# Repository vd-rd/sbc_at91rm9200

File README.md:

## Overview
This module, based on Microchip (Atmel) AT91RM9200 microprocessor, is intended as a learning exercise in designing an embedded Linux development board suitable for IoT and other applications.
 All the board resources and documentation are open source and can be contributed to.
 Detailed documentation, as well as resources used can be found in the [docs](docs) and [resources](resources) folders.

### Key features
 * Low price for an embedded Linux system;
 * Medium difficulty to assemble at home;
 * Documented features and mainline support in kernel.

### Specifications
  * AT91RM9200 microprocessor @ 190MHz;
  * 64MB SDRAM @ 90MHz;
  * 2MB DataFlash memory for U-boot and environment storage;
  * MicroSD connector for RootFS and user storage;
  * Expansion headers with common functions available (USART, SPI, I2C, RMII, USB Host, etc.);
  * USB client connector.

### Todo
 * build the board
 * gather the components
 * test the board
 * build optimised U-Boot and Busybox

### Resources
You can find all necesary information to build or evaluate the module here:
   - [View layout and schematic](https://cadlab.io/project/1679) ;
   - [View 3D board render](https://a360.co/2G43pcl);
   - [Fabrication files](https://github.com/vd-rd/sbc_at91rm9200/releases);

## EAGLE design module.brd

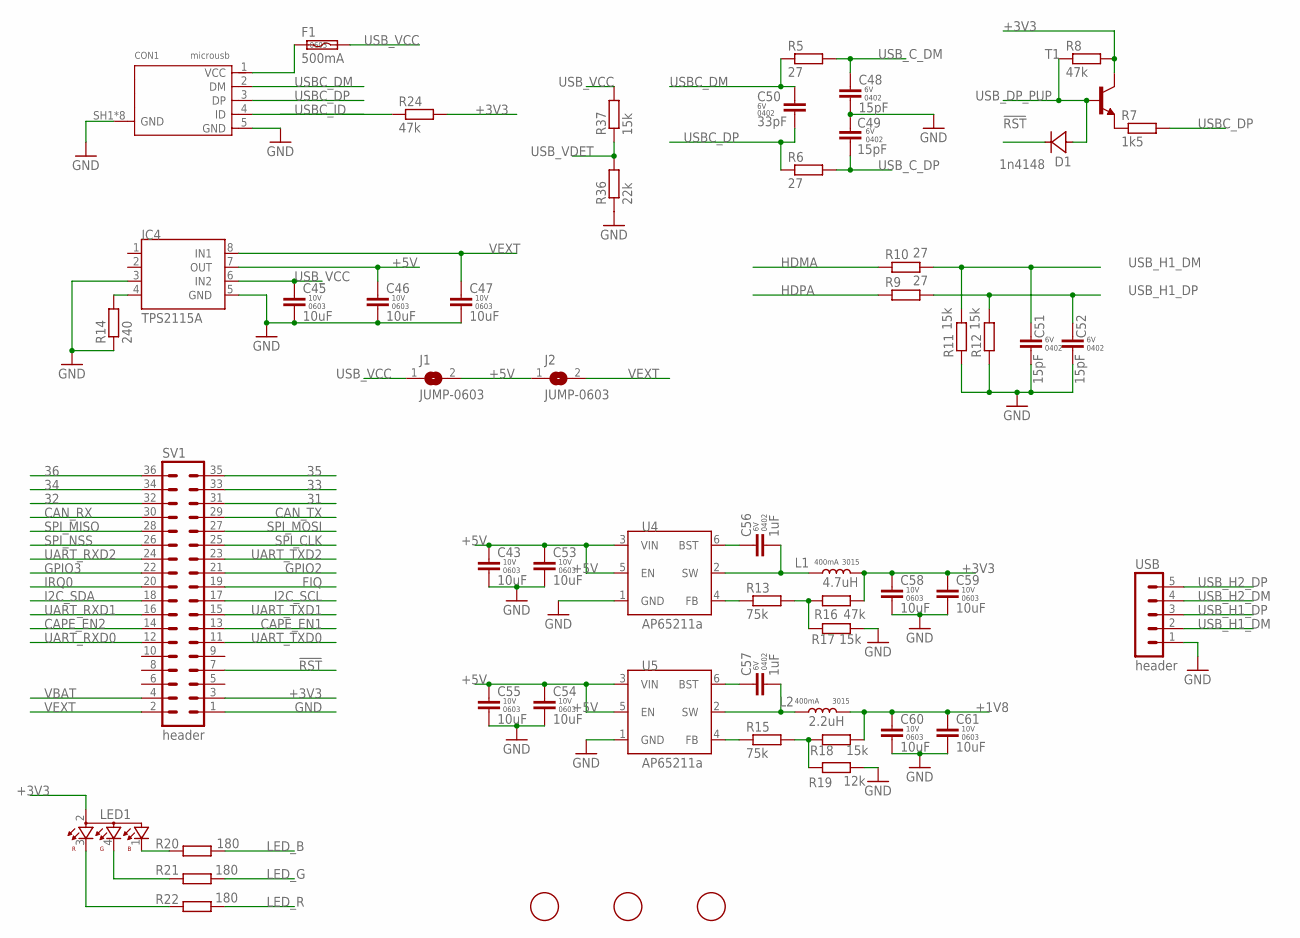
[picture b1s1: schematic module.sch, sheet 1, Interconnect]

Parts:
C43, C45, C46, C47, C53, C54, C55, C58, C59, C60, C61: 10uF; C0603
C48, C49, C51, C52: 15pF; C0402K
C50: 33pF; C0402K
C56, C57: 1uF; C0402K
CON1: microusb; 10118194
D1: 1n4148; SOD323
F1: 500mA; F0603
IC4: TPS2115A; TSSOP8
J1, J2: JUMP-0603; C0603
L1: 4.7uH; L3230M
L2: 2.2uH; L3230M
LED1: OSTB1204C1E; 321015RGB
R5, R6, R9, R10: 27; R0402
R7: 1k5; R0402
R8, R16, R24: 47k; R0402
R11, R12, R17, R18, R37: 15k; R0402
R13, R15: 75k; R0402
R14: 240; R0402
R19: 12k; R0402
R20, R21, R22: 180; R0402
R36: 22k; R0402
SV1: header; MA18-2
T1: MMBT2222ALT1-NPN-SOT23-BEC; SOT23-BEC
U4, U5: AP65211A; SOT95P280X110-6
U$1, U$2, U$3: FIDUCIAL; FIDUCIAL_1MM
USB: header; MA05-1

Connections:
31: SV1.31; also elsewhere on the board
32: SV1.32; also elsewhere on the board
33: SV1.33; also elsewhere on the board
34: SV1.34; also elsewhere on the board
35: SV1.35; also elsewhere on the board
36: SV1.36; also elsewhere on the board
!RST: D1.K (C), SV1.7; also elsewhere on the board
+1V8: C60.1, C61.1, L2.2, R18.2; also elsewhere on the board
+3V3: C58.1, C59.1, L1.2, LED1.2, R8.2, R16.2, R24.2, SV1.3, T1.C; also elsewhere on the board
+5V: C43.1, C46.1, C53.1, C54.1, C55.1, IC4.7 (OUT), J1.2, J2.1, U4.3 (VIN), U4.5 (EN), U5.3 (VIN), U5.5 (EN)
CAN_RX: SV1.30
CAN_TX: SV1.29
CAPE_EN1: SV1.13; also elsewhere on the board
CAPE_EN2: SV1.14; also elsewhere on the board
FIQ: SV1.19; also elsewhere on the board
GND: C43.2, C45.2, C46.2, C47.2, C48.2, C49.2, C51.2, C52.2, C53.2, C54.2, C55.2, C58.2, C59.2, C60.2, C61.2, CON1.5 (GND), CON1.SH1 (GND), CON1.SH2 (GND), CON1.SH3 (GND), CON1.SH4 (GND), CON1.SH5 (GND), CON1.SH6 (GND), CON1.SH7 (GND), CON1.SH8 (GND), IC4.3, IC4.5 (GND), R11.1, R12.1, R14.1, R17.2, R19.2, R36.1, SV1.1, U4.1 (GND), U5.1 (GND), USB.1; also elsewhere on the board
GPIO2: SV1.21; also elsewhere on the board
GPIO3: SV1.22; also elsewhere on the board
HDMA: R10.1; also elsewhere on the board
HDPA: R9.1; also elsewhere on the board
I2C_SCL: SV1.17; also elsewhere on the board
I2C_SDA: SV1.18; also elsewhere on the board
IRQ0: SV1.20; also elsewhere on the board
LED_B: R20.1; also elsewhere on the board
LED_G: R21.1; also elsewhere on the board
LED_R: R22.1; also elsewhere on the board
unnamed: C56.2, L1.1, U4.2 (SW)
unnamed: CON1.1 (VCC), F1.1
unnamed: IC4.4, R14.2
unnamed: C57.2, L2.1, U5.2 (SW)
unnamed: LED1.1, R20.2
unnamed: C56.1, U4.6 (BST)
unnamed: C57.1, U5.6 (BST)
unnamed: LED1.4, R21.2
unnamed: R15.1, U5.4 (FB)
unnamed: R7.1, T1.E
unnamed: R13.1, U4.4 (FB)
unnamed: R15.2, R18.1, R19.1
unnamed: R13.2, R16.1, R17.1
unnamed: LED1.3, R22.2
SPI_CLK: SV1.25; also elsewhere on the board
SPI_MISO: SV1.28; also elsewhere on the board
SPI_MOSI: SV1.27; also elsewhere on the board
SPI_NSS: SV1.26; also elsewhere on the board
UART_RXD0: SV1.12; also elsewhere on the board
UART_RXD1: SV1.16; also elsewhere on the board
UART_RXD2: SV1.24; also elsewhere on the board
UART_TXD0: SV1.11; also elsewhere on the board
UART_TXD1: SV1.15; also elsewhere on the board
UART_TXD2: SV1.23; also elsewhere on the board
USBC_DM: C50.1, CON1.2 (DM), R5.1
USBC_DP: C50.2, CON1.3 (DP), R6.1, R7.2
USBC_ID: CON1.4 (ID), R24.1; also elsewhere on the board
USB_C_DM: C48.1, R5.2; also elsewhere on the board
USB_C_DP: C49.1, R6.2; also elsewhere on the board
USB_DP_PUP: D1.A, R8.1, T1.B; also elsewhere on the board
USB_H1_DM: C51.1, R10.2, R11.2, USB.2
USB_H1_DP: C52.1, R9.2, R12.2, USB.3
USB_H2_DM: USB.4
USB_H2_DP: USB.5
USB_VCC: C45.1, F1.2, IC4.6 (IN2), J1.1, R37.2
USB_VDET: R36.2, R37.1; also elsewhere on the board
VBAT: SV1.4
VEXT: C47.1, IC4.8 (IN1), J2.2, SV1.2

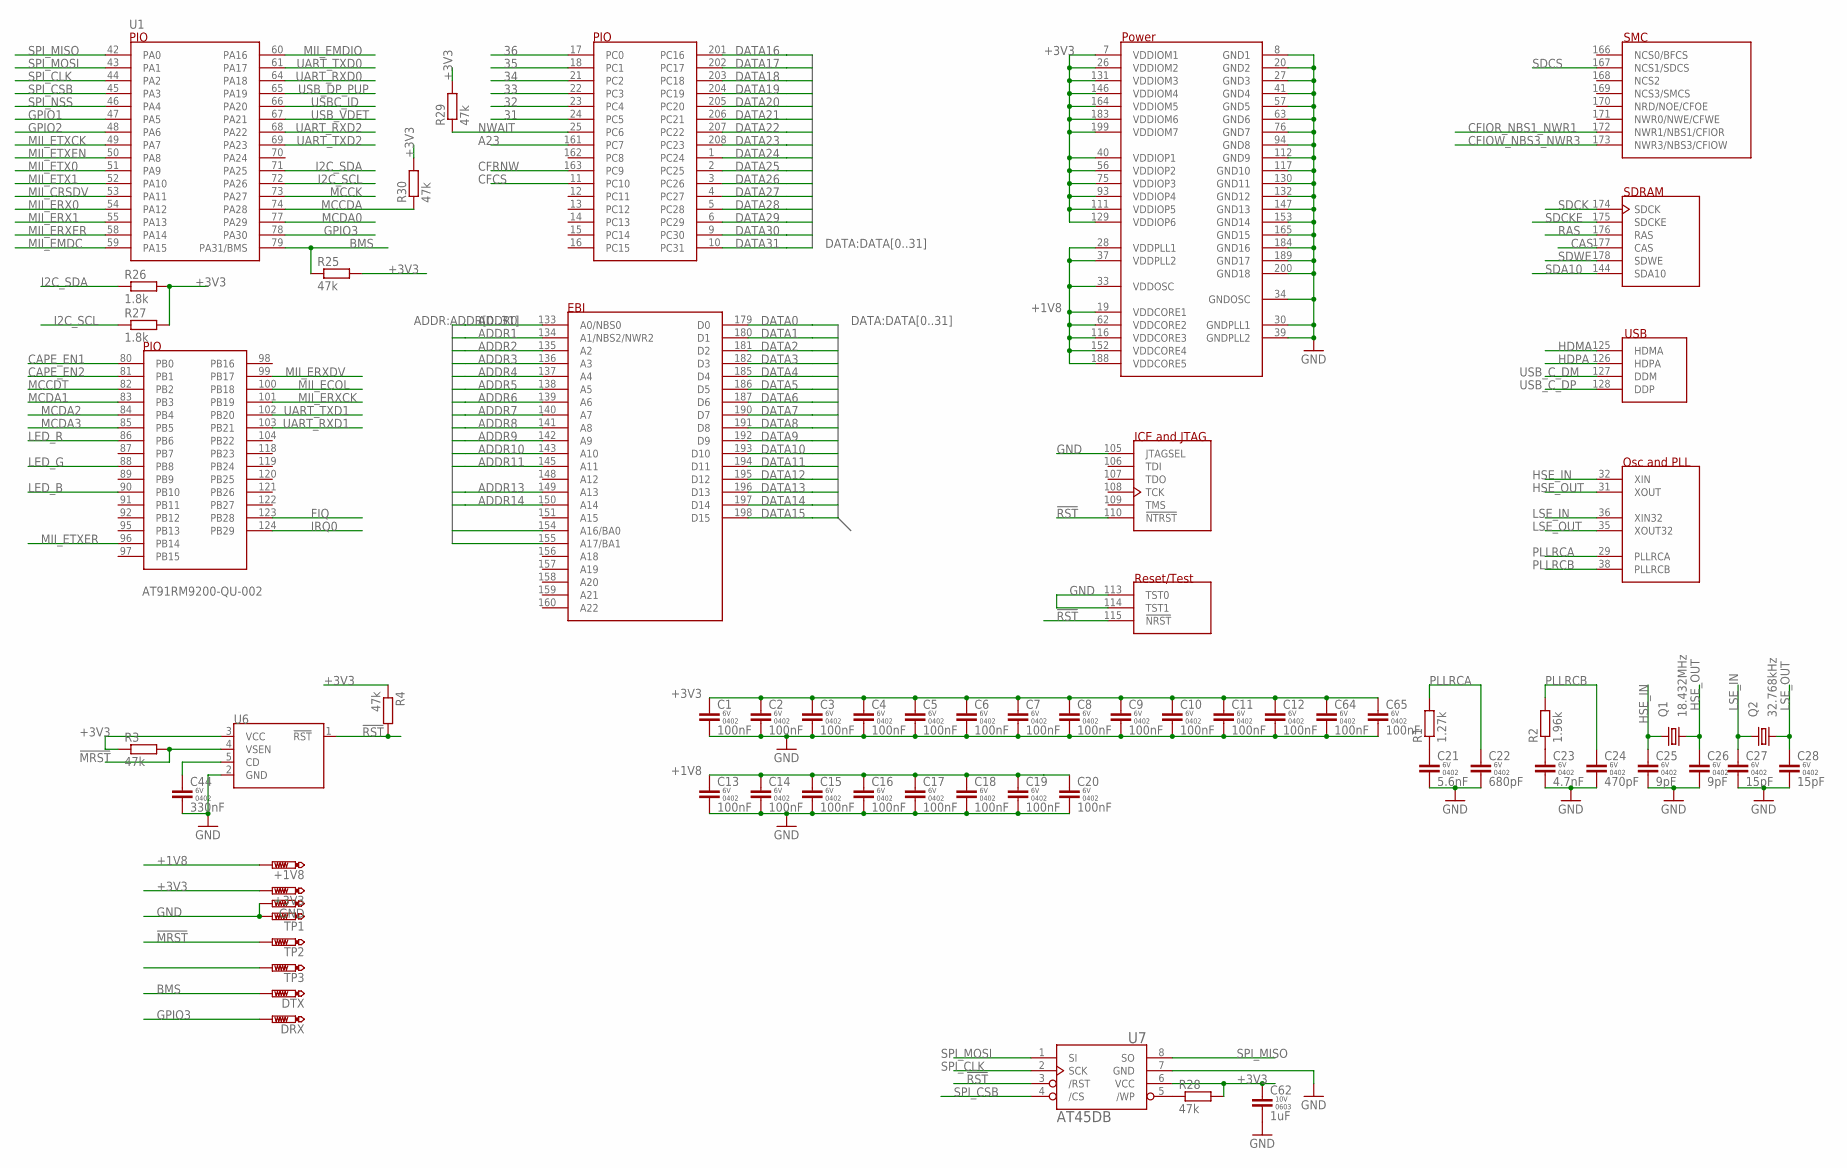
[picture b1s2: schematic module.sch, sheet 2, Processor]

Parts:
+1V8, +3V3: PTR1B1,27; B1,27
C1, C2, C3, C4, C5, C6, C7, C8, C9, C10, C11, C12, C13, C14, C15, C16, C17, C18, C19, C20, C64, C65: 100nF; C0402K
C21: 5.6nF; C0402K
C22: 680pF; C0402K
C23: 4.7nF; C0402K
C24: 470pF; C0402K
C25, C26: 9pF; C0402K
C27, C28: 15pF; C0402K
C44: 330nF; C0402K
C62: 1uF; C0603
DRX: PTR1B1,27; B1,27
DTX: PTR1B1,27; B1,27
GND: PTR1B1,27; B1,27
Q1: 18.432MHz; 3215
Q2: 32.768kHz; 3215
R1: 1.27k; R0402
R2: 1.96k; R0402
R3, R4, R25, R28, R29, R30: 47k; R0402
R26, R27: 1.8k; R0402
TP1, TP2, TP3: PTR1B1,27; B1,27
U1: AT91RM9200-QU-002; QFP50P3120X3120X410-208N
U6: STM1831; SOT95P280X100-5
U7: AT45DB-S; SO08-208

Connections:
31: U1.24 (PC5); also elsewhere on the board
32: U1.23 (PC4); also elsewhere on the board
33: U1.22 (PC3); also elsewhere on the board
34: U1.21 (PC2); also elsewhere on the board
35: U1.18 (PC1); also elsewhere on the board
36: U1.17 (PC0); also elsewhere on the board
!MRST: R3.2, TP2.TP, U6.4 (VSEN)
!RST: R4.2, U1.110 (!NTRST), U1.115 (!NRST), U6.1 (!RST), U7.3 (/RST); also elsewhere on the board
+1V8: +1V8.TP, C13.1, C14.1, C15.1, C16.1, C17.1, C18.1, C19.1, C20.1, U1.19 (VDDCORE1), U1.28 (VDDPLL1), U1.33 (VDDOSC), U1.37 (VDDPLL2), U1.62 (VDDCORE2), U1.116 (VDDCORE3), U1.152 (VDDCORE4), U1.188 (VDDCORE5); also elsewhere on the board
+3V3: +3V3.TP, C1.1, C2.1, C3.1, C4.1, C5.1, C6.1, C7.1, C8.1, C9.1, C10.1, C11.1, C12.1, C62.1, C64.1, C65.1, R3.1, R4.1, R25.2, R26.2, R27.2, R28.2, R29.2, R30.2, U1.7 (VDDIOM1), U1.26 (VDDIOM2), U1.40 (VDDIOP1), U1.56 (VDDIOP2), U1.75 (VDDIOP3), U1.93 (VDDIOP4), U1.111 (VDDIOP5), U1.129 (VDDIOP6), U1.131 (VDDIOM3), U1.146 (VDDIOM4), U1.164 (VDDIOM5), U1.183 (VDDIOM6), U1.199 (VDDIOM7), U6.3 (VCC), U7.6 (VCC); also elsewhere on the board
A23: U1.161 (PC7)
ADDR0: U1.133 (A0/NBS0); also elsewhere on the board
ADDR1: U1.134 (A1/NBS2/NWR2); also elsewhere on the board
ADDR2: U1.135 (A2); also elsewhere on the board
ADDR3: U1.136 (A3); also elsewhere on the board
ADDR4: U1.137 (A4); also elsewhere on the board
ADDR5: U1.138 (A5); also elsewhere on the board
ADDR6: U1.139 (A6); also elsewhere on the board
ADDR7: U1.140 (A7); also elsewhere on the board
ADDR8: U1.141 (A8); also elsewhere on the board
ADDR9: U1.142 (A9); also elsewhere on the board
ADDR10: U1.143 (A10); also elsewhere on the board
ADDR11: U1.145 (A11); also elsewhere on the board
ADDR13: U1.149 (A13); also elsewhere on the board
ADDR14: U1.150 (A14); also elsewhere on the board
ADDR16: U1.154 (A16/BA0); also elsewhere on the board
ADDR17: U1.155 (A17/BA1); also elsewhere on the board
BMS: DTX.TP, R25.1, U1.79 (PA31/BMS)
CAPE_EN1: U1.80 (PB0); also elsewhere on the board
CAPE_EN2: U1.81 (PB1); also elsewhere on the board
CAS: U1.177 (CAS); also elsewhere on the board
CFCS: U1.11 (PC10)
CFIOR_NBS1_NWR1: U1.172 (NWR1/NBS1/CFIOR); also elsewhere on the board
CFIOW_NBS3_NWR3: U1.173 (NWR3/NBS3/CFIOW); also elsewhere on the board
CFRNW: U1.163 (PC9)
DATA0: U1.179 (D0); also elsewhere on the board
DATA1: U1.180 (D1); also elsewhere on the board
DATA2: U1.181 (D2); also elsewhere on the board
DATA3: U1.182 (D3); also elsewhere on the board
DATA4: U1.185 (D4); also elsewhere on the board
DATA5: U1.186 (D5); also elsewhere on the board
DATA6: U1.187 (D6); also elsewhere on the board
DATA7: U1.190 (D7); also elsewhere on the board
DATA8: U1.191 (D8); also elsewhere on the board
DATA9: U1.192 (D9); also elsewhere on the board
DATA10: U1.193 (D10); also elsewhere on the board
DATA11: U1.194 (D11); also elsewhere on the board
DATA12: U1.195 (D12); also elsewhere on the board
DATA13: U1.196 (D13); also elsewhere on the board
DATA14: U1.197 (D14); also elsewhere on the board
DATA15: U1.198 (D15); also elsewhere on the board
DATA16: U1.201 (PC16); also elsewhere on the board
DATA17: U1.202 (PC17); also elsewhere on the board
DATA18: U1.203 (PC18); also elsewhere on the board
DATA19: U1.204 (PC19); also elsewhere on the board
DATA20: U1.205 (PC20); also elsewhere on the board
DATA21: U1.206 (PC21); also elsewhere on the board
DATA22: U1.207 (PC22); also elsewhere on the board
DATA23: U1.208 (PC23); also elsewhere on the board
DATA24: U1.1 (PC24); also elsewhere on the board
DATA25: U1.2 (PC25); also elsewhere on the board
DATA26: U1.3 (PC26); also elsewhere on the board
DATA27: U1.4 (PC27); also elsewhere on the board
DATA28: U1.5 (PC28); also elsewhere on the board
DATA29: U1.6 (PC29); also elsewhere on the board
DATA30: U1.9 (PC30); also elsewhere on the board
DATA31: U1.10 (PC31); also elsewhere on the board
FIQ: U1.123 (PB28); also elsewhere on the board
GND: C1.2, C2.2, C3.2, C4.2, C5.2, C6.2, C7.2, C8.2, C9.2, C10.2, C11.2, C12.2, C13.2, C14.2, C15.2, C16.2, C17.2, C18.2, C19.2, C20.2, C21.2, C22.2, C23.2, C24.2, C25.2, C26.2, C27.2, C28.2, C44.2, C62.2, C64.2, C65.2, GND.TP, TP1.TP, U1.8 (GND1), U1.20 (GND2), U1.27 (GND3), U1.30 (GNDPLL1), U1.34 (GNDOSC), U1.39 (GNDPLL2), U1.41 (GND4), U1.57 (GND5), U1.63 (GND6), U1.76 (GND7), U1.94 (GND8), U1.105 (JTAGSEL), U1.112 (GND9), U1.113 (TST0), U1.114 (TST1), U1.117 (GND10), U1.130 (GND11), U1.132 (GND12), U1.147 (GND13), U1.153 (GND14), U1.165 (GND15), U1.184 (GND16), U1.189 (GND17), U1.200 (GND18), U6.2 (GND), U7.7 (GND); also elsewhere on the board
GPIO1: U1.47 (PA5)
GPIO2: U1.48 (PA6); also elsewhere on the board
GPIO3: DRX.TP, U1.78 (PA30); also elsewhere on the board
HDMA: U1.125 (HDMA); also elsewhere on the board
HDPA: U1.126 (HDPA); also elsewhere on the board
HSE_IN: C25.1, Q1.1, U1.32 (XIN)
HSE_OUT: C26.1, Q1.3 (2), U1.31 (XOUT)
I2C_SCL: R27.1, U1.72 (PA26); also elsewhere on the board
I2C_SDA: R26.1, U1.71 (PA25); also elsewhere on the board
IRQ0: U1.124 (PB29); also elsewhere on the board
LED_B: U1.90 (PB10); also elsewhere on the board
LED_G: U1.88 (PB8); also elsewhere on the board
LED_R: U1.86 (PB6); also elsewhere on the board
LSE_IN: C27.1, Q2.1, U1.36 (XIN32)
LSE_OUT: C28.1, Q2.2, U1.35 (XOUT32)
MCCDA: R30.1, U1.74 (PA28); also elsewhere on the board
MCCDT: U1.82 (PB2); also elsewhere on the board
MCCK: U1.73 (PA27); also elsewhere on the board
MCDA0: U1.77 (PA29); also elsewhere on the board
MCDA1: U1.83 (PB3); also elsewhere on the board
MCDA2: U1.84 (PB4); also elsewhere on the board
MCDA3: U1.85 (PB5); also elsewhere on the board
MII_CRSDV: U1.53 (PA11); also elsewhere on the board
MII_ECOL: U1.100 (PB18)
MII_EMDC: U1.59 (PA15); also elsewhere on the board
MII_EMDIO: U1.60 (PA16); also elsewhere on the board
MII_ERX0: U1.54 (PA12); also elsewhere on the board
MII_ERX1: U1.55 (PA13); also elsewhere on the board
MII_ERXCK: U1.101 (PB19)
MII_ERXDV: U1.99 (PB17)
MII_ERXER: U1.58 (PA14); also elsewhere on the board
MII_ETX0: U1.51 (PA9); also elsewhere on the board
MII_ETX1: U1.52 (PA10); also elsewhere on the board
MII_ETXCK: U1.49 (PA7); also elsewhere on the board
MII_ETXEN: U1.50 (PA8); also elsewhere on the board
MII_ETXER: U1.96 (PB14)
unnamed: C21.1, R1.1
unnamed: C23.1, R2.1
unnamed: R28.1, U7.5 (/WP)
unnamed: C44.1, U6.5 (CD)
NWAIT: R29.1, U1.25 (PC6)
PLLRCA: C22.1, R1.2, U1.29 (PLLRCA)
PLLRCB: C24.1, R2.2, U1.38 (PLLRCB)
RAS: U1.176 (RAS); also elsewhere on the board
SDA10: U1.144 (SDA10); also elsewhere on the board
SDCK: U1.174 (SDCK); also elsewhere on the board
SDCKE: U1.175 (SDCKE); also elsewhere on the board
SDCS: U1.167 (NCS1/SDCS); also elsewhere on the board
SDWE: U1.178 (SDWE); also elsewhere on the board
SPI_CLK: U1.44 (PA2), U7.2 (SCK); also elsewhere on the board
SPI_CSB: U1.45 (PA3), U7.4 (/CS)
SPI_MISO: U1.42 (PA0), U7.8 (SO); also elsewhere on the board
SPI_MOSI: U1.43 (PA1), U7.1 (SI); also elsewhere on the board
SPI_NSS: U1.46 (PA4); also elsewhere on the board
UART_RXD0: U1.64 (PA18); also elsewhere on the board
UART_RXD1: U1.103 (PB21); also elsewhere on the board
UART_RXD2: U1.68 (PA22); also elsewhere on the board
UART_TXD0: U1.61 (PA17); also elsewhere on the board
UART_TXD1: U1.102 (PB20); also elsewhere on the board
UART_TXD2: U1.69 (PA23); also elsewhere on the board
USBC_ID: U1.66 (PA20); also elsewhere on the board
USB_C_DM: U1.127 (DDM); also elsewhere on the board
USB_C_DP: U1.128 (DDP); also elsewhere on the board
USB_DP_PUP: U1.65 (PA19); also elsewhere on the board
USB_VDET: U1.67 (PA21); also elsewhere on the board

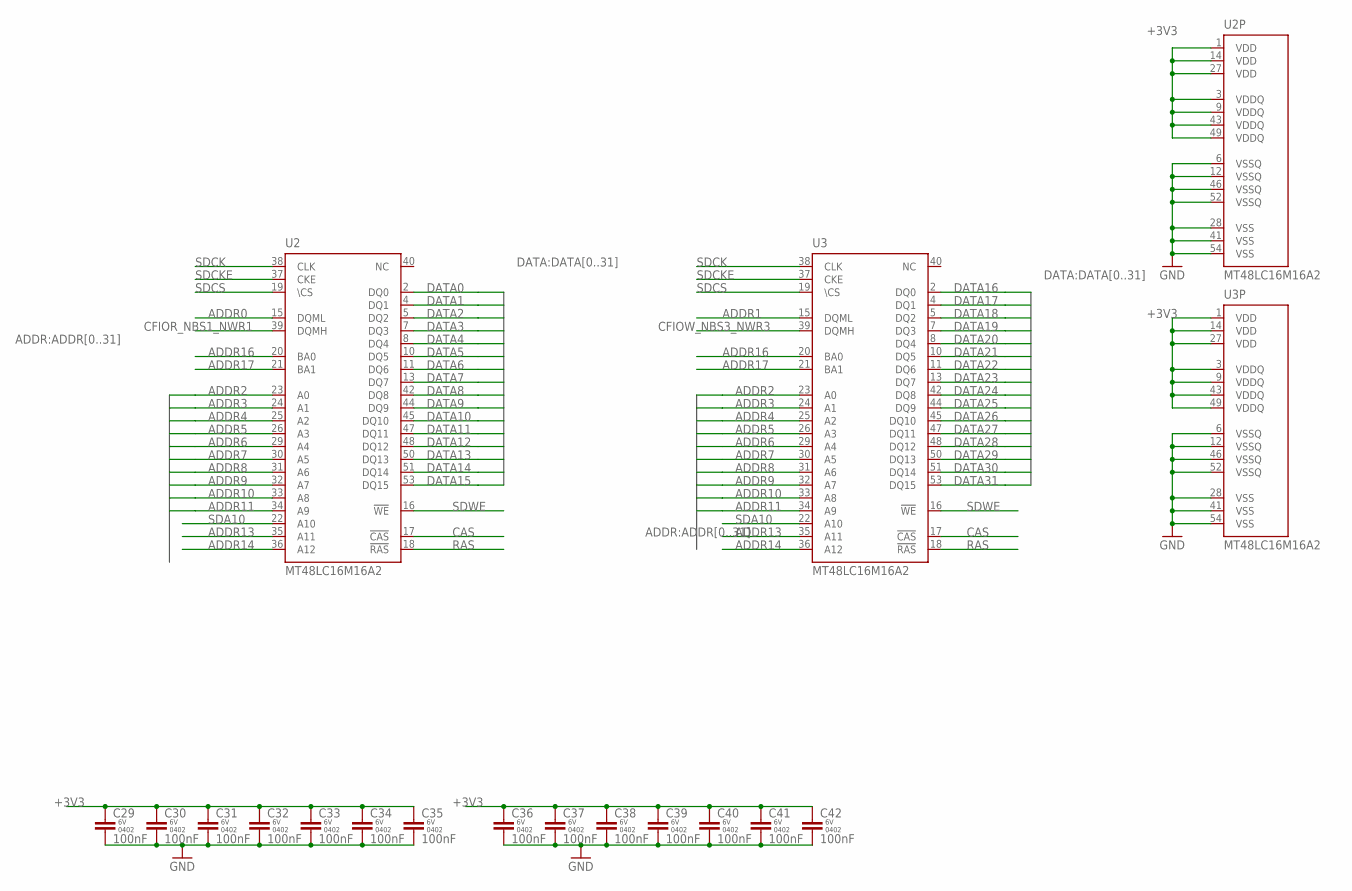
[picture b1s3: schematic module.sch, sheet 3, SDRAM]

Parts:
C29, C30, C31, C32, C33, C34, C35, C36, C37, C38, C39, C40, C41, C42: 100nF; C0402K
U2, U3: MT48LC16M16A2; TSOP54-400

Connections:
+3V3: C29.1, C30.1, C31.1, C32.1, C33.1, C34.1, C35.1, C36.1, C37.1, C38.1, C39.1, C40.1, C41.1, C42.1, U2.1 (VDD), U2.3 (VDDQ), U2.9 (VDDQ), U2.14 (VDD), U2.27 (VDD), U2.43 (VDDQ), U2.49 (VDDQ), U3.1 (VDD), U3.3 (VDDQ), U3.9 (VDDQ), U3.14 (VDD), U3.27 (VDD), U3.43 (VDDQ), U3.49 (VDDQ); also elsewhere on the board
ADDR0: U2.15 (DQML); also elsewhere on the board
ADDR1: U3.15 (DQML); also elsewhere on the board
ADDR2: U2.23 (A0), U3.23 (A0); also elsewhere on the board
ADDR3: U2.24 (A1), U3.24 (A1); also elsewhere on the board
ADDR4: U2.25 (A2), U3.25 (A2); also elsewhere on the board
ADDR5: U2.26 (A3), U3.26 (A3); also elsewhere on the board
ADDR6: U2.29 (A4), U3.29 (A4); also elsewhere on the board
ADDR7: U2.30 (A5), U3.30 (A5); also elsewhere on the board
ADDR8: U2.31 (A6), U3.31 (A6); also elsewhere on the board
ADDR9: U2.32 (A7), U3.32 (A7); also elsewhere on the board
ADDR10: U2.33 (A8), U3.33 (A8); also elsewhere on the board
ADDR11: U2.34 (A9), U3.34 (A9); also elsewhere on the board
ADDR13: U2.35 (A11), U3.35 (A11); also elsewhere on the board
ADDR14: U2.36 (A12), U3.36 (A12); also elsewhere on the board
ADDR16: U2.20 (BA0), U3.20 (BA0); also elsewhere on the board
ADDR17: U2.21 (BA1), U3.21 (BA1); also elsewhere on the board
CAS: U2.17 (!CAS), U3.17 (!CAS); also elsewhere on the board
CFIOR_NBS1_NWR1: U2.39 (DQMH); also elsewhere on the board
CFIOW_NBS3_NWR3: U3.39 (DQMH); also elsewhere on the board
DATA0: U2.2 (DQ0); also elsewhere on the board
DATA1: U2.4 (DQ1); also elsewhere on the board
DATA2: U2.5 (DQ2); also elsewhere on the board
DATA3: U2.7 (DQ3); also elsewhere on the board
DATA4: U2.8 (DQ4); also elsewhere on the board
DATA5: U2.10 (DQ5); also elsewhere on the board
DATA6: U2.11 (DQ6); also elsewhere on the board
DATA7: U2.13 (DQ7); also elsewhere on the board
DATA8: U2.42 (DQ8); also elsewhere on the board
DATA9: U2.44 (DQ9); also elsewhere on the board
DATA10: U2.45 (DQ10); also elsewhere on the board
DATA11: U2.47 (DQ11); also elsewhere on the board
DATA12: U2.48 (DQ12); also elsewhere on the board
DATA13: U2.50 (DQ13); also elsewhere on the board
DATA14: U2.51 (DQ14); also elsewhere on the board
DATA15: U2.53 (DQ15); also elsewhere on the board
DATA16: U3.2 (DQ0); also elsewhere on the board
DATA17: U3.4 (DQ1); also elsewhere on the board
DATA18: U3.5 (DQ2); also elsewhere on the board
DATA19: U3.7 (DQ3); also elsewhere on the board
DATA20: U3.8 (DQ4); also elsewhere on the board
DATA21: U3.10 (DQ5); also elsewhere on the board
DATA22: U3.11 (DQ6); also elsewhere on the board
DATA23: U3.13 (DQ7); also elsewhere on the board
DATA24: U3.42 (DQ8); also elsewhere on the board
DATA25: U3.44 (DQ9); also elsewhere on the board
DATA26: U3.45 (DQ10); also elsewhere on the board
DATA27: U3.47 (DQ11); also elsewhere on the board
DATA28: U3.48 (DQ12); also elsewhere on the board
DATA29: U3.50 (DQ13); also elsewhere on the board
DATA30: U3.51 (DQ14); also elsewhere on the board
DATA31: U3.53 (DQ15); also elsewhere on the board
GND: C29.2, C30.2, C31.2, C32.2, C33.2, C34.2, C35.2, C36.2, C37.2, C38.2, C39.2, C40.2, C41.2, C42.2, U2.6 (VSSQ), U2.12 (VSSQ), U2.28 (VSS), U2.41 (VSS), U2.46 (VSSQ), U2.52 (VSSQ), U2.54 (VSS), U3.6 (VSSQ), U3.12 (VSSQ), U3.28 (VSS), U3.41 (VSS), U3.46 (VSSQ), U3.52 (VSSQ), U3.54 (VSS); also elsewhere on the board
RAS: U2.18 (!RAS), U3.18 (!RAS); also elsewhere on the board
SDA10: U2.22 (A10), U3.22 (A10); also elsewhere on the board
SDCK: U2.38 (CLK), U3.38 (CLK); also elsewhere on the board
SDCKE: U2.37 (CKE), U3.37 (CKE); also elsewhere on the board
SDCS: U2.19 (\CS), U3.19 (\CS); also elsewhere on the board
SDWE: U2.16 (!WE), U3.16 (!WE); also elsewhere on the board

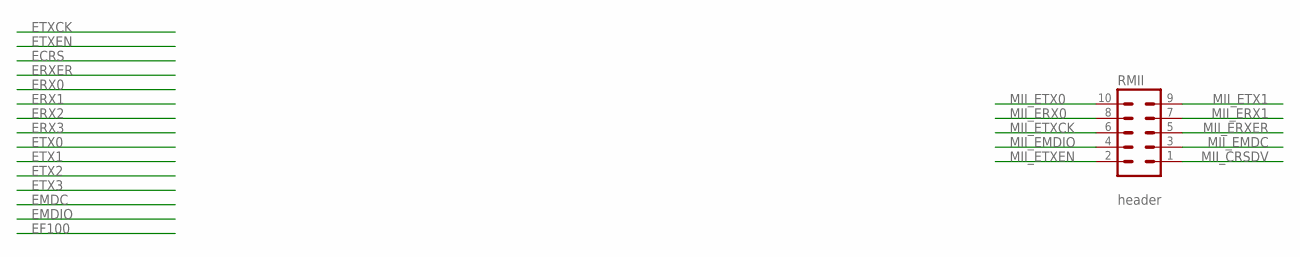
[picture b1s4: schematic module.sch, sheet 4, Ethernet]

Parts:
RMII: header; MA05-2

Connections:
MII_CRSDV: RMII.1; also elsewhere on the board
MII_EMDC: RMII.3; also elsewhere on the board
MII_EMDIO: RMII.4; also elsewhere on the board
MII_ERX0: RMII.8; also elsewhere on the board
MII_ERX1: RMII.7; also elsewhere on the board
MII_ERXER: RMII.5; also elsewhere on the board
MII_ETX0: RMII.10; also elsewhere on the board
MII_ETX1: RMII.9; also elsewhere on the board
MII_ETXCK: RMII.6; also elsewhere on the board
MII_ETXEN: RMII.2; also elsewhere on the board

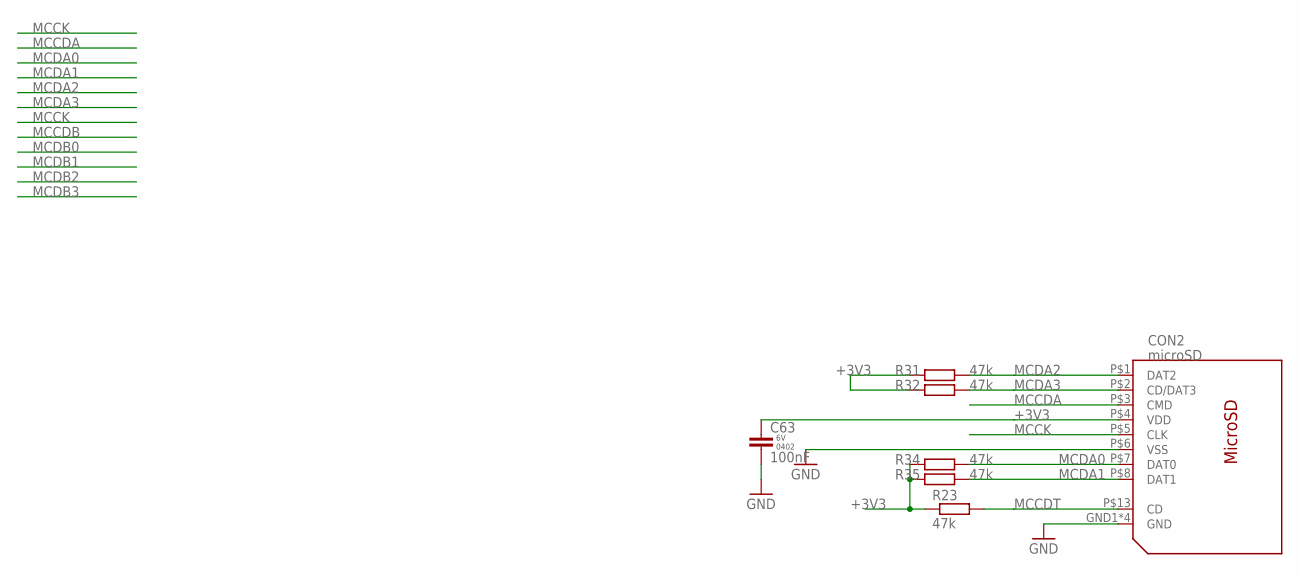
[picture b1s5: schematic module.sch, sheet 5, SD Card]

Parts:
C63: 100nF; C0402K
CON2: microSD; 112J
R23, R31, R32, R34, R35: 47k; R0402

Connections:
+3V3: C63.1, CON2.P$4 (VDD), R23.1, R31.1, R32.1, R34.1, R35.1; also elsewhere on the board
GND: C63.2, CON2.GND1 (GND), CON2.GND2 (GND), CON2.GND3 (GND), CON2.GND4 (GND), CON2.P$6 (VSS); also elsewhere on the board
MCCDA: CON2.P$3 (CMD); also elsewhere on the board
MCCDT: CON2.P$13 (CD), R23.2; also elsewhere on the board
MCCK: CON2.P$5 (CLK); also elsewhere on the board
MCDA0: CON2.P$7 (DAT0), R34.2; also elsewhere on the board
MCDA1: CON2.P$8 (DAT1), R35.2; also elsewhere on the board
MCDA2: CON2.P$1 (DAT2), R31.2; also elsewhere on the board
MCDA3: CON2.P$2 (CD/DAT3), R32.2; also elsewhere on the board

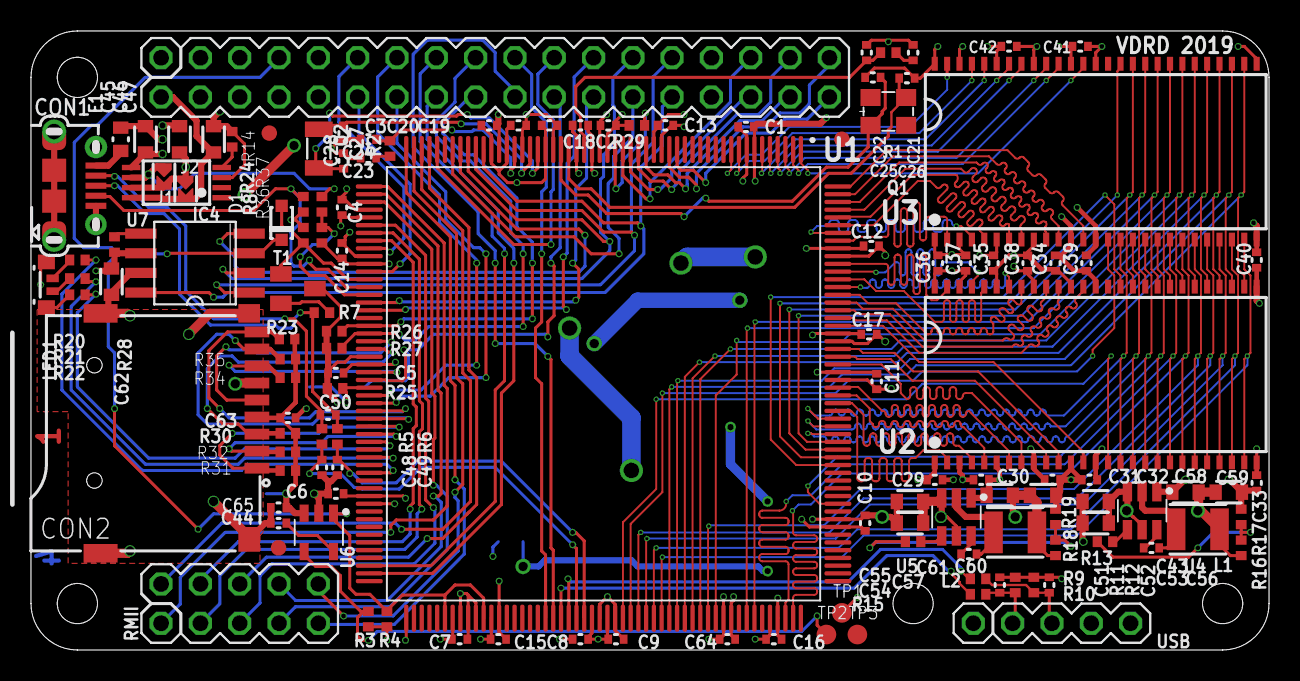
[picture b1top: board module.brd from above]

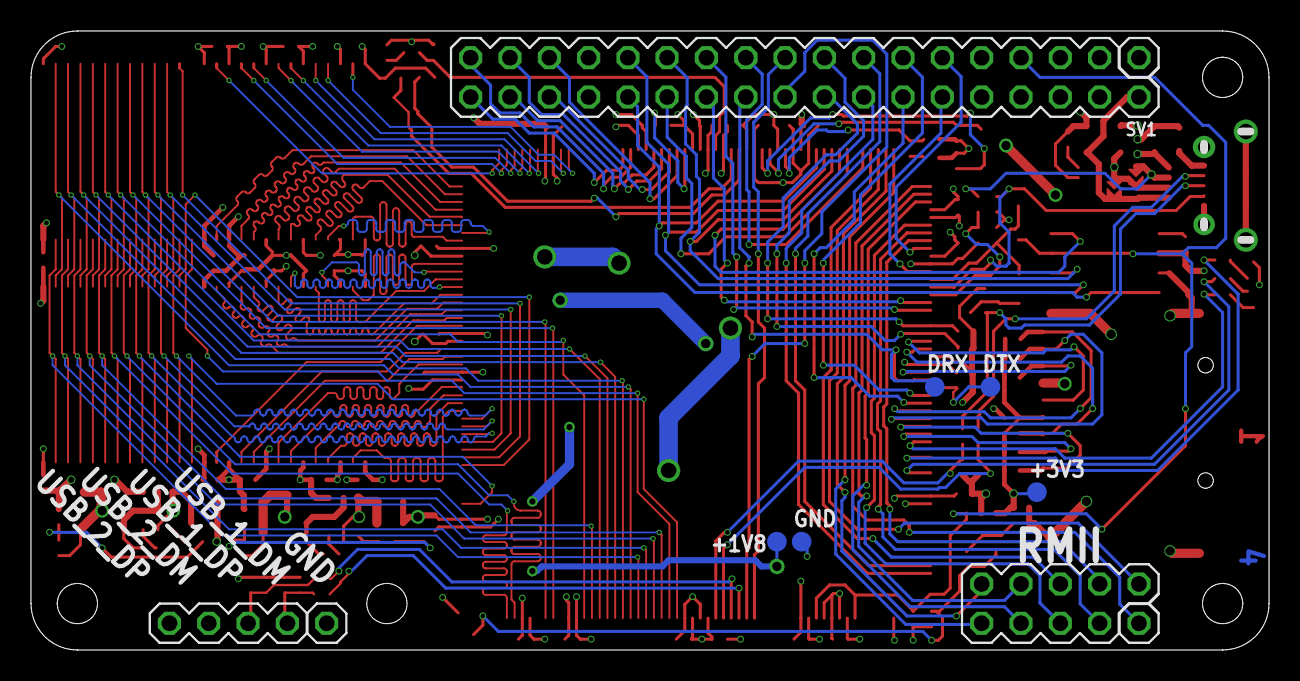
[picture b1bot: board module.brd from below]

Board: 4 copper layers, 80.0 x 40.0 mm, 135 parts (6 on the bottom side), 147 nets.

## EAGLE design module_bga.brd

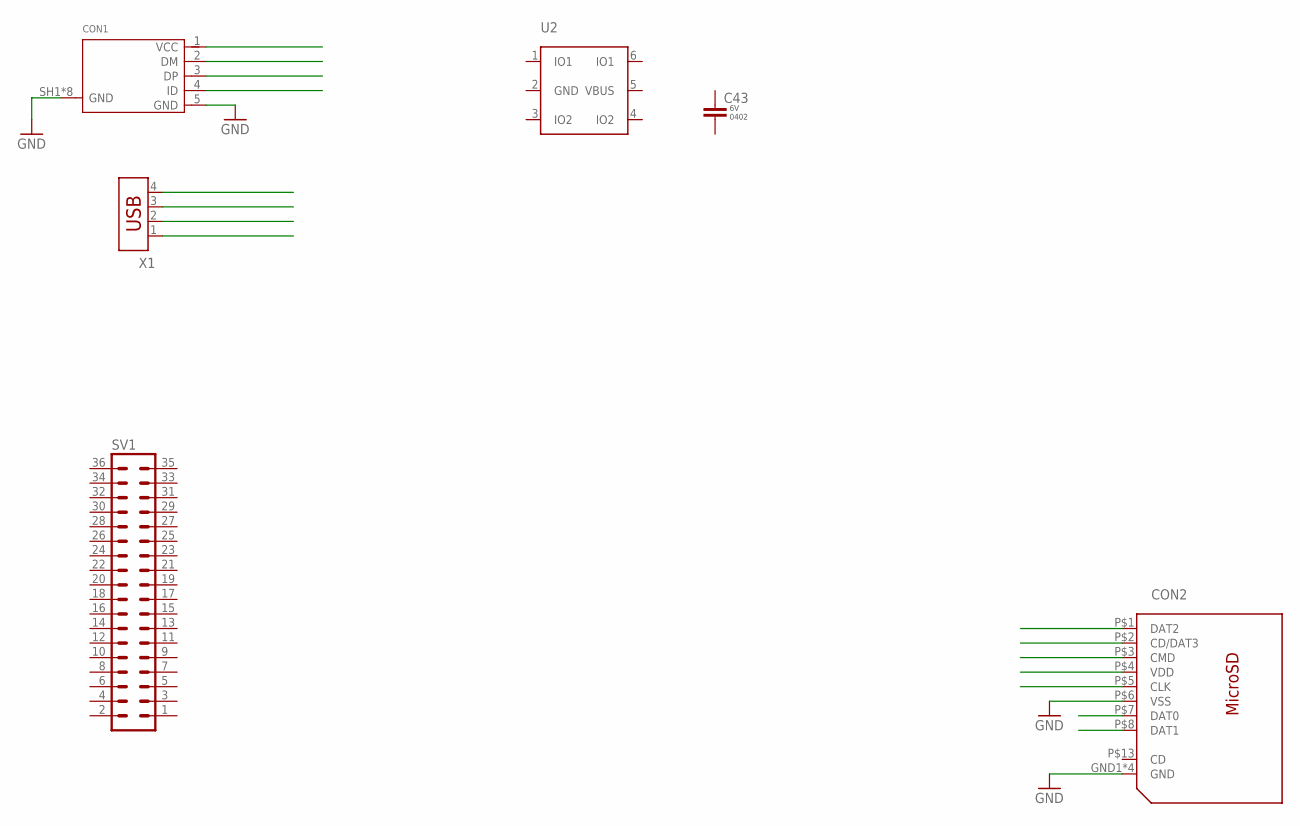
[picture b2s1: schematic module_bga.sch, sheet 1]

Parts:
C43: CAP-0402; C0402K
CON1: 10118194-0001LF; 10118194
CON2: 112J-TXAR; 112J
SV1: MA18-2
U2: USBLC6-2SC6; SOT95P280X110-6
X1: USB-787616; USB

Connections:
DAT0@7: CON2.P$7 (DAT0)
DAT1@8: CON2.P$8 (DAT1)
GND: CON1.5 (GND), CON1.SH1 (GND), CON1.SH2 (GND), CON1.SH3 (GND), CON1.SH4 (GND), CON1.SH5 (GND), CON1.SH6 (GND), CON1.SH7 (GND), CON1.SH8 (GND), CON2.GND1 (GND), CON2.GND2 (GND), CON2.GND3 (GND), CON2.GND4 (GND), CON2.P$6 (VSS); also elsewhere on the board

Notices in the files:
parts and their libraries:
crystal-geyer_V1_0: Copyright: Geyer-Electronic
